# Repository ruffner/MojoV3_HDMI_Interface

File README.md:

# Dual HDMI + Camera Interface PCB for 120Hz SLI

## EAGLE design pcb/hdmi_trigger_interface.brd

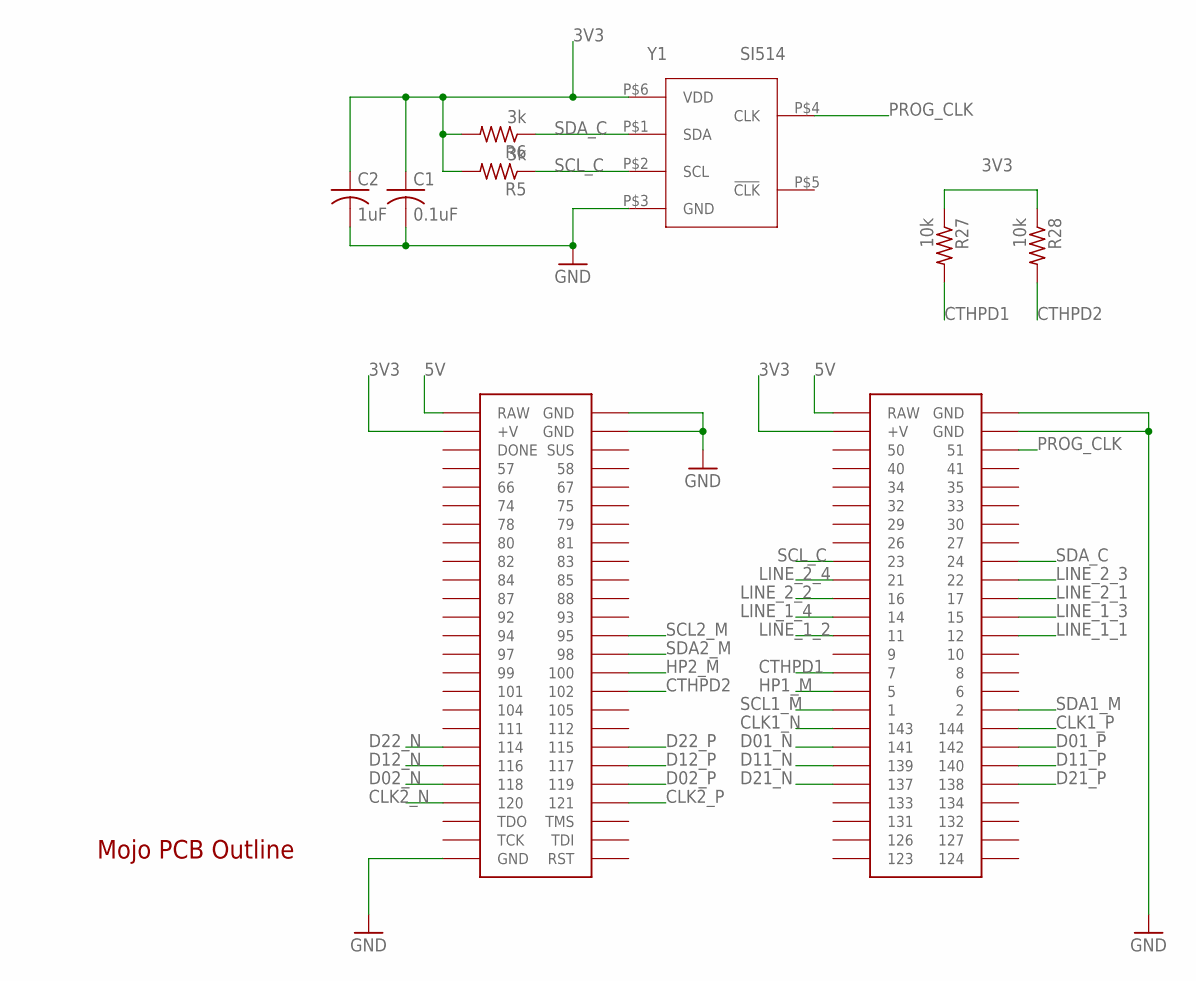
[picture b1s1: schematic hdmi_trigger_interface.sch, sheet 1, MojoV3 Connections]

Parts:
C1: 0.1uF; C0603
C2: 1uF; C0603
R5, R6: 3k; R0603
R27, R28: 10k; R0603
U$1: MOJOV3; MOJO_V3
U$2: MOJO_OUTLINE
Y1: SI514; XTAL-6PIN

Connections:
3V3: C1.1, C2.1, R5.2, R6.2, R27.1, R28.1, U$1.V@1 (+V), U$1.V@2 (+V), Y1.P$6 (VDD); also elsewhere on the board
5V: U$1.RAW@1 (RAW), U$1.RAW@2 (RAW); also elsewhere on the board
CLK1_N: U$1.143; also elsewhere on the board
CLK1_P: U$1.144; also elsewhere on the board
CLK2_N: U$1.120; also elsewhere on the board
CLK2_P: U$1.121; also elsewhere on the board
CTHPD1: R27.2, U$1.7; also elsewhere on the board
CTHPD2: R28.2, U$1.102; also elsewhere on the board
D01_N: U$1.141; also elsewhere on the board
D01_P: U$1.142; also elsewhere on the board
D02_N: U$1.118; also elsewhere on the board
D02_P: U$1.119; also elsewhere on the board
D11_N: U$1.139; also elsewhere on the board
D11_P: U$1.140; also elsewhere on the board
D12_N: U$1.116; also elsewhere on the board
D12_P: U$1.117; also elsewhere on the board
D21_N: U$1.137; also elsewhere on the board
D21_P: U$1.138; also elsewhere on the board
D22_N: U$1.114; also elsewhere on the board
D22_P: U$1.115; also elsewhere on the board
GND: C1.2, C2.2, U$1.GND@1 (GND), U$1.GND@2 (GND), U$1.GND@3 (GND), U$1.GND@4 (GND), U$1.GND@6 (GND), Y1.P$3 (GND); also elsewhere on the board
HP1_M: U$1.5; also elsewhere on the board
HP2_M: U$1.100; also elsewhere on the board
LINE_1_1: U$1.12; also elsewhere on the board
LINE_1_2: U$1.11; also elsewhere on the board
LINE_1_3: U$1.15; also elsewhere on the board
LINE_1_4: U$1.14; also elsewhere on the board
LINE_2_1: U$1.17; also elsewhere on the board
LINE_2_2: U$1.16; also elsewhere on the board
LINE_2_3: U$1.22; also elsewhere on the board
LINE_2_4: U$1.21; also elsewhere on the board
PROG_CLK: U$1.51, Y1.P$4 (CLK)
SCL1_M: U$1.1; also elsewhere on the board
SCL2_M: U$1.95; also elsewhere on the board
SCL_C: R5.1, U$1.23, Y1.P$2 (SCL)
SDA1_M: U$1.2; also elsewhere on the board
SDA2_M: U$1.98; also elsewhere on the board
SDA_C: R6.1, U$1.24, Y1.P$1 (SDA)

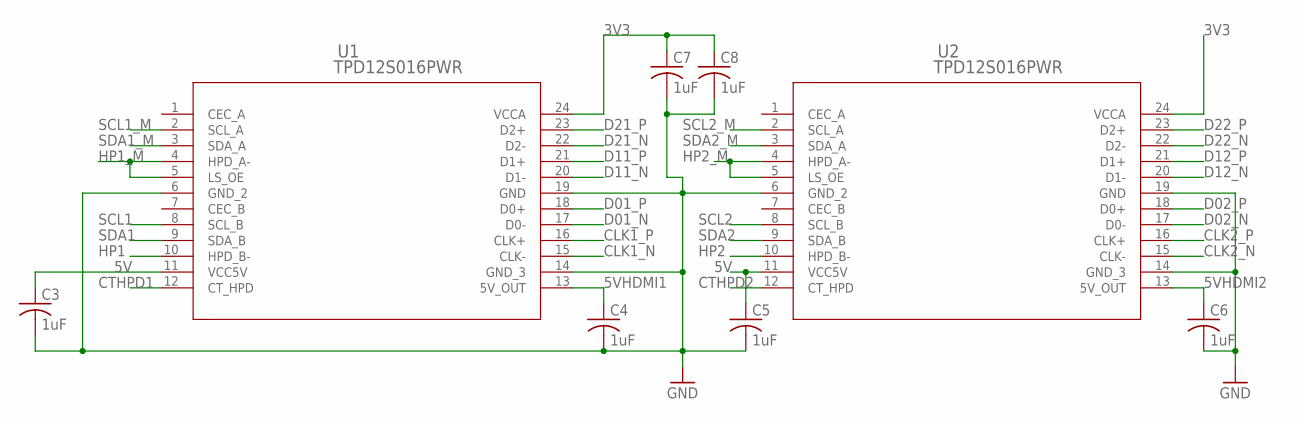
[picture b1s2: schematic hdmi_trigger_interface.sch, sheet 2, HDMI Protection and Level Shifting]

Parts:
C3, C4, C5, C6, C7, C8: 1uF; C0603
U1, U2: TPD12S016PWR; PW24

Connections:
3V3: C7.1, C8.1, U1.24 (VCCA), U2.24 (VCCA); also elsewhere on the board
5V: C3.1, C5.1, U1.11 (VCC5V), U2.11 (VCC5V); also elsewhere on the board
5VHDMI1: C4.1, U1.13 (5V_OUT); also elsewhere on the board
5VHDMI2: C6.1, U2.13 (5V_OUT); also elsewhere on the board
CLK1_N: U1.15 (CLK-); also elsewhere on the board
CLK1_P: U1.16 (CLK+); also elsewhere on the board
CLK2_N: U2.15 (CLK-); also elsewhere on the board
CLK2_P: U2.16 (CLK+); also elsewhere on the board
CTHPD1: U1.12 (CT_HPD); also elsewhere on the board
CTHPD2: U2.12 (CT_HPD); also elsewhere on the board
D01_N: U1.17 (D0-); also elsewhere on the board
D01_P: U1.18 (D0+); also elsewhere on the board
D02_N: U2.17 (D0-); also elsewhere on the board
D02_P: U2.18 (D0+); also elsewhere on the board
D11_N: U1.20 (D1-); also elsewhere on the board
D11_P: U1.21 (D1+); also elsewhere on the board
D12_N: U2.20 (D1-); also elsewhere on the board
D12_P: U2.21 (D1+); also elsewhere on the board
D21_N: U1.22 (D2-); also elsewhere on the board
D21_P: U1.23 (D2+); also elsewhere on the board
D22_N: U2.22 (D2-); also elsewhere on the board
D22_P: U2.23 (D2+); also elsewhere on the board
GND: C3.2, C4.2, C5.2, C6.2, C7.2, C8.2, U1.6 (GND_2), U1.14 (GND_3), U1.19 (GND), U2.6 (GND_2), U2.14 (GND_3), U2.19 (GND); also elsewhere on the board
HP1: U1.10 (HPD_B-); also elsewhere on the board
HP1_M: U1.4 (HPD_A-), U1.5 (LS_OE); also elsewhere on the board
HP2: U2.10 (HPD_B-); also elsewhere on the board
HP2_M: U2.4 (HPD_A-), U2.5 (LS_OE); also elsewhere on the board
SCL1: U1.8 (SCL_B); also elsewhere on the board
SCL1_M: U1.2 (SCL_A); also elsewhere on the board
SCL2: U2.8 (SCL_B); also elsewhere on the board
SCL2_M: U2.2 (SCL_A); also elsewhere on the board
SDA1: U1.9 (SDA_B); also elsewhere on the board
SDA1_M: U1.3 (SDA_A); also elsewhere on the board
SDA2: U2.9 (SDA_B); also elsewhere on the board
SDA2_M: U2.3 (SDA_A); also elsewhere on the board

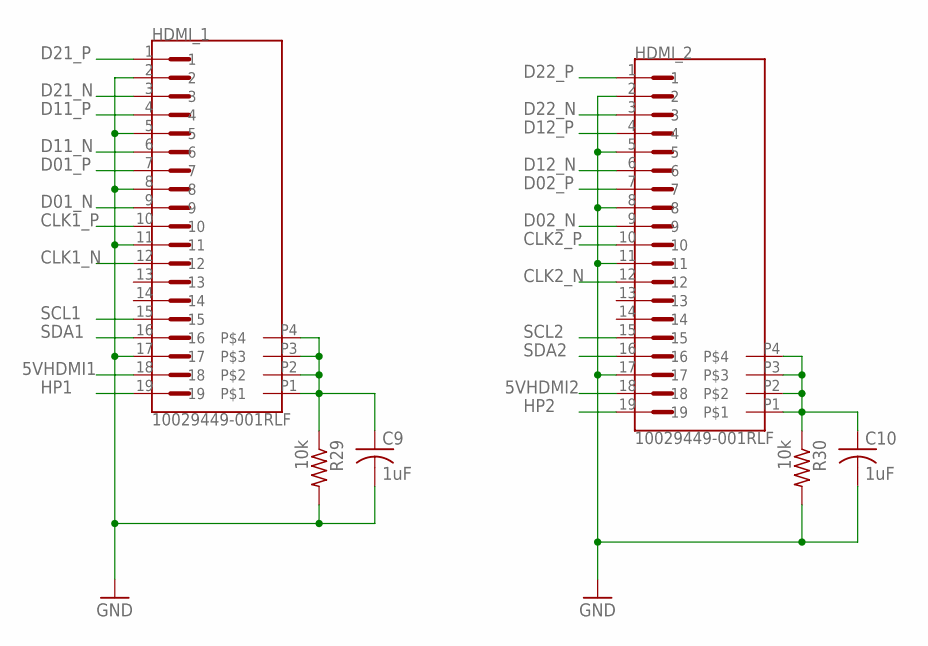
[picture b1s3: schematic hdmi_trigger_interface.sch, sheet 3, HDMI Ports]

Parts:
C9, C10: 1uF; C0603
HDMI_1, HDMI_2: 10029449-001RLF; FCI_10029449-001RLF
R29, R30: 10k; R0603

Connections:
5VHDMI1: HDMI_1.18; also elsewhere on the board
5VHDMI2: HDMI_2.18; also elsewhere on the board
CLK1_N: HDMI_1.12; also elsewhere on the board
CLK1_P: HDMI_1.10; also elsewhere on the board
CLK2_N: HDMI_2.12; also elsewhere on the board
CLK2_P: HDMI_2.10; also elsewhere on the board
D01_N: HDMI_1.9; also elsewhere on the board
D01_P: HDMI_1.7; also elsewhere on the board
D02_N: HDMI_2.9; also elsewhere on the board
D02_P: HDMI_2.7; also elsewhere on the board
D11_N: HDMI_1.6; also elsewhere on the board
D11_P: HDMI_1.4; also elsewhere on the board
D12_N: HDMI_2.6; also elsewhere on the board
D12_P: HDMI_2.4; also elsewhere on the board
D21_N: HDMI_1.3; also elsewhere on the board
D21_P: HDMI_1.1; also elsewhere on the board
D22_N: HDMI_2.3; also elsewhere on the board
D22_P: HDMI_2.1; also elsewhere on the board
GND: C9.2, C10.2, HDMI_1.2, HDMI_1.5, HDMI_1.8, HDMI_1.11, HDMI_1.17, HDMI_2.2, HDMI_2.5, HDMI_2.8, HDMI_2.11, HDMI_2.17, R29.2, R30.2; also elsewhere on the board
HP1: HDMI_1.19; also elsewhere on the board
HP2: HDMI_2.19; also elsewhere on the board
unnamed: C9.1, HDMI_1.P1, HDMI_1.P2, HDMI_1.P3, HDMI_1.P4, R29.1
unnamed: C10.1, HDMI_2.P1, HDMI_2.P2, HDMI_2.P3, HDMI_2.P4, R30.1
SCL1: HDMI_1.15; also elsewhere on the board
SCL2: HDMI_2.15; also elsewhere on the board
SDA1: HDMI_1.16; also elsewhere on the board
SDA2: HDMI_2.16; also elsewhere on the board

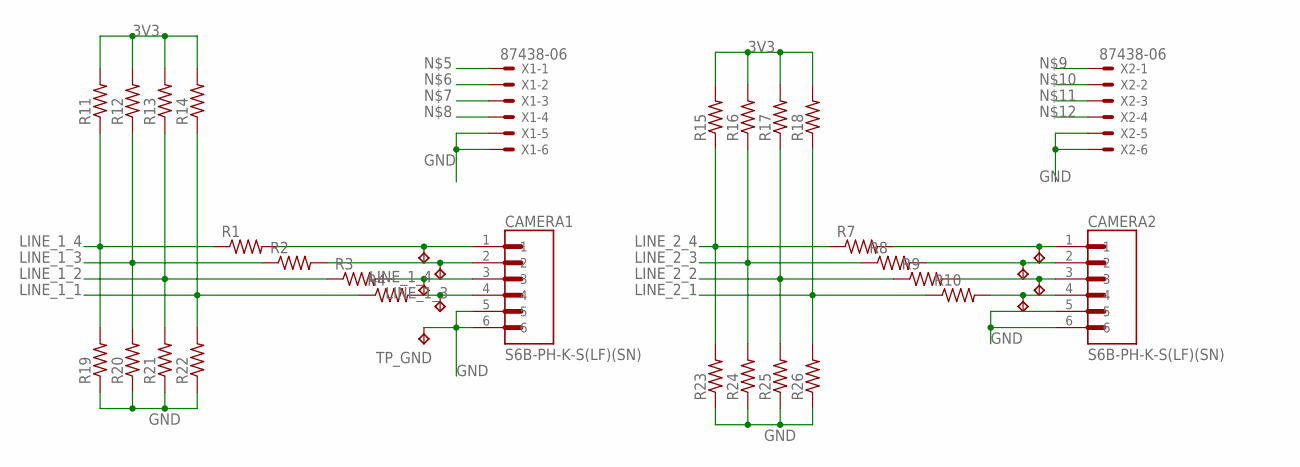
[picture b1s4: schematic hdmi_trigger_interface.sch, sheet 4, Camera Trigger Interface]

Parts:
CAMERA1, CAMERA2: S6B-PH-K-S(LF)(SN); JST_S6B-PH-K-S(LF)(SN)
LINE_1_1, LINE_1_2, LINE_1_3, LINE_1_4: TPTP16R; TP16R
LINE_2_1, LINE_4: LINE_1; TP16R
LINE_2_2: LINE_2; TP16R
LINE_2_3: LINE_3; TP16R
R1, R2, R3, R4, R7, R8, R9, R10, R11, R12, R13, R14, R15, R16, R17, R18, R19, R20, R21, R22, R23, R24, R25, R26: R-US_R0603; R0603
TP_GND: TPTP16R; TP16R
X1, X2: 87438-06

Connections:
3V3: R11.2, R12.2, R13.2, R14.2, R15.2, R16.2, R17.2, R18.2; also elsewhere on the board
GND: CAMERA1.5, CAMERA1.6, CAMERA2.5, CAMERA2.6, R19.1, R20.1, R21.1, R22.1, R23.1, R24.1, R25.1, R26.1, TP_GND.TP, X1.5, X1.6, X2.5, X2.6; also elsewhere on the board
LINE_1_1: R4.1, R14.1, R22.2; also elsewhere on the board
LINE_1_2: R3.1, R13.1, R21.2; also elsewhere on the board
LINE_1_3: R2.1, R12.1, R20.2; also elsewhere on the board
LINE_1_4: R1.1, R11.1, R19.2; also elsewhere on the board
LINE_2_1: R10.1, R18.1, R26.2; also elsewhere on the board
LINE_2_2: R9.1, R17.1, R25.2; also elsewhere on the board
LINE_2_3: R8.1, R16.1, R24.2; also elsewhere on the board
LINE_2_4: R7.1, R15.1, R23.2; also elsewhere on the board
unnamed: CAMERA1.1, LINE_1_4.TP, R1.2, X1.1
unnamed: CAMERA1.2, LINE_1_3.TP, R2.2, X1.2
unnamed: CAMERA1.3, LINE_1_2.TP, R3.2, X1.3
unnamed: CAMERA1.4, LINE_1_1.TP, R4.2, X1.4
unnamed: CAMERA2.1, LINE_4.TP, R7.2, X2.1
unnamed: CAMERA2.2, LINE_2_3.TP, R8.2, X2.2
unnamed: CAMERA2.3, LINE_2_2.TP, R9.2, X2.3
unnamed: CAMERA2.4, LINE_2_1.TP, R10.2, X2.4

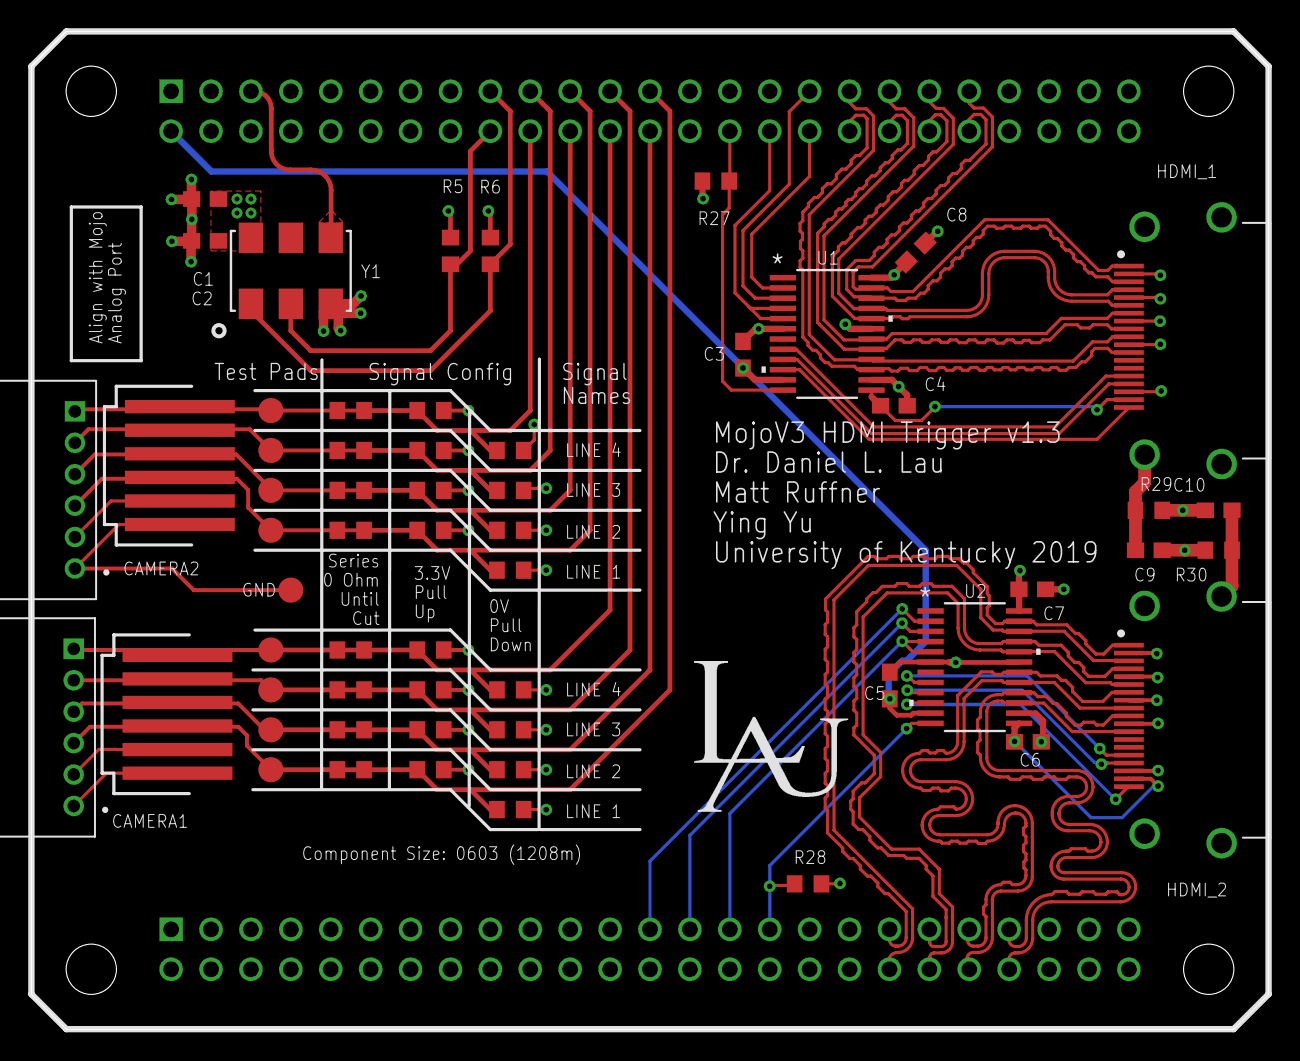
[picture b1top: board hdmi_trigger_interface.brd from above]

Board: 4 copper layers, 78.7 x 63.5 mm, 60 parts (0 on the bottom side), 56 nets.

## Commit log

2019-01-21 initial commit with pcb outline and html5 up template
2019-01-21 work on hdmi integration into basler trigger circuitry
2019-01-22 almost done with routing
2019-01-23 board layout 90% done, need parts list then will order
2019-01-24 added images from manufacturing render and gerbers sent to pcbway
2019-02-12 rerouting with a 4 layer board and 7.6mil traces and 6mil spacing for 100 ohm differential impedance' g
2019-02-12 more routing
2019-02-13 hdmi differential pairs routed and length tunedgit status
2019-02-13 spacing tweaks
2019-02-14 length tuning and routing done, need final review then ready to order
2019-02-14 final tweaks
2019-02-28 added .gitignore file
2019-02-28 added conn library
2019-03-01 ripped up old diff pairs, ready to route new 8/8 lines
2019-03-05 one hdmi port routed, one to go. net class made with 8/8 mil trace width and spacing
2019-03-05 started routing second hdmi port
2019-03-06 work on routing second hdmi port
2019-03-18 more work on length tuning
2019-03-20 finished routing with new spacing and layout.
2019-03-20 final tweak
2019-03-20 added previous and current gerbers
2019-03-20 added 4 layer pcbway cam file
2019-03-20 removed desktop.ini
2019-05-29 added power supply mount
2025-01-01 add DB9 MOJO shield and DB9 Numato shield
2025-01-01 remove web docs
